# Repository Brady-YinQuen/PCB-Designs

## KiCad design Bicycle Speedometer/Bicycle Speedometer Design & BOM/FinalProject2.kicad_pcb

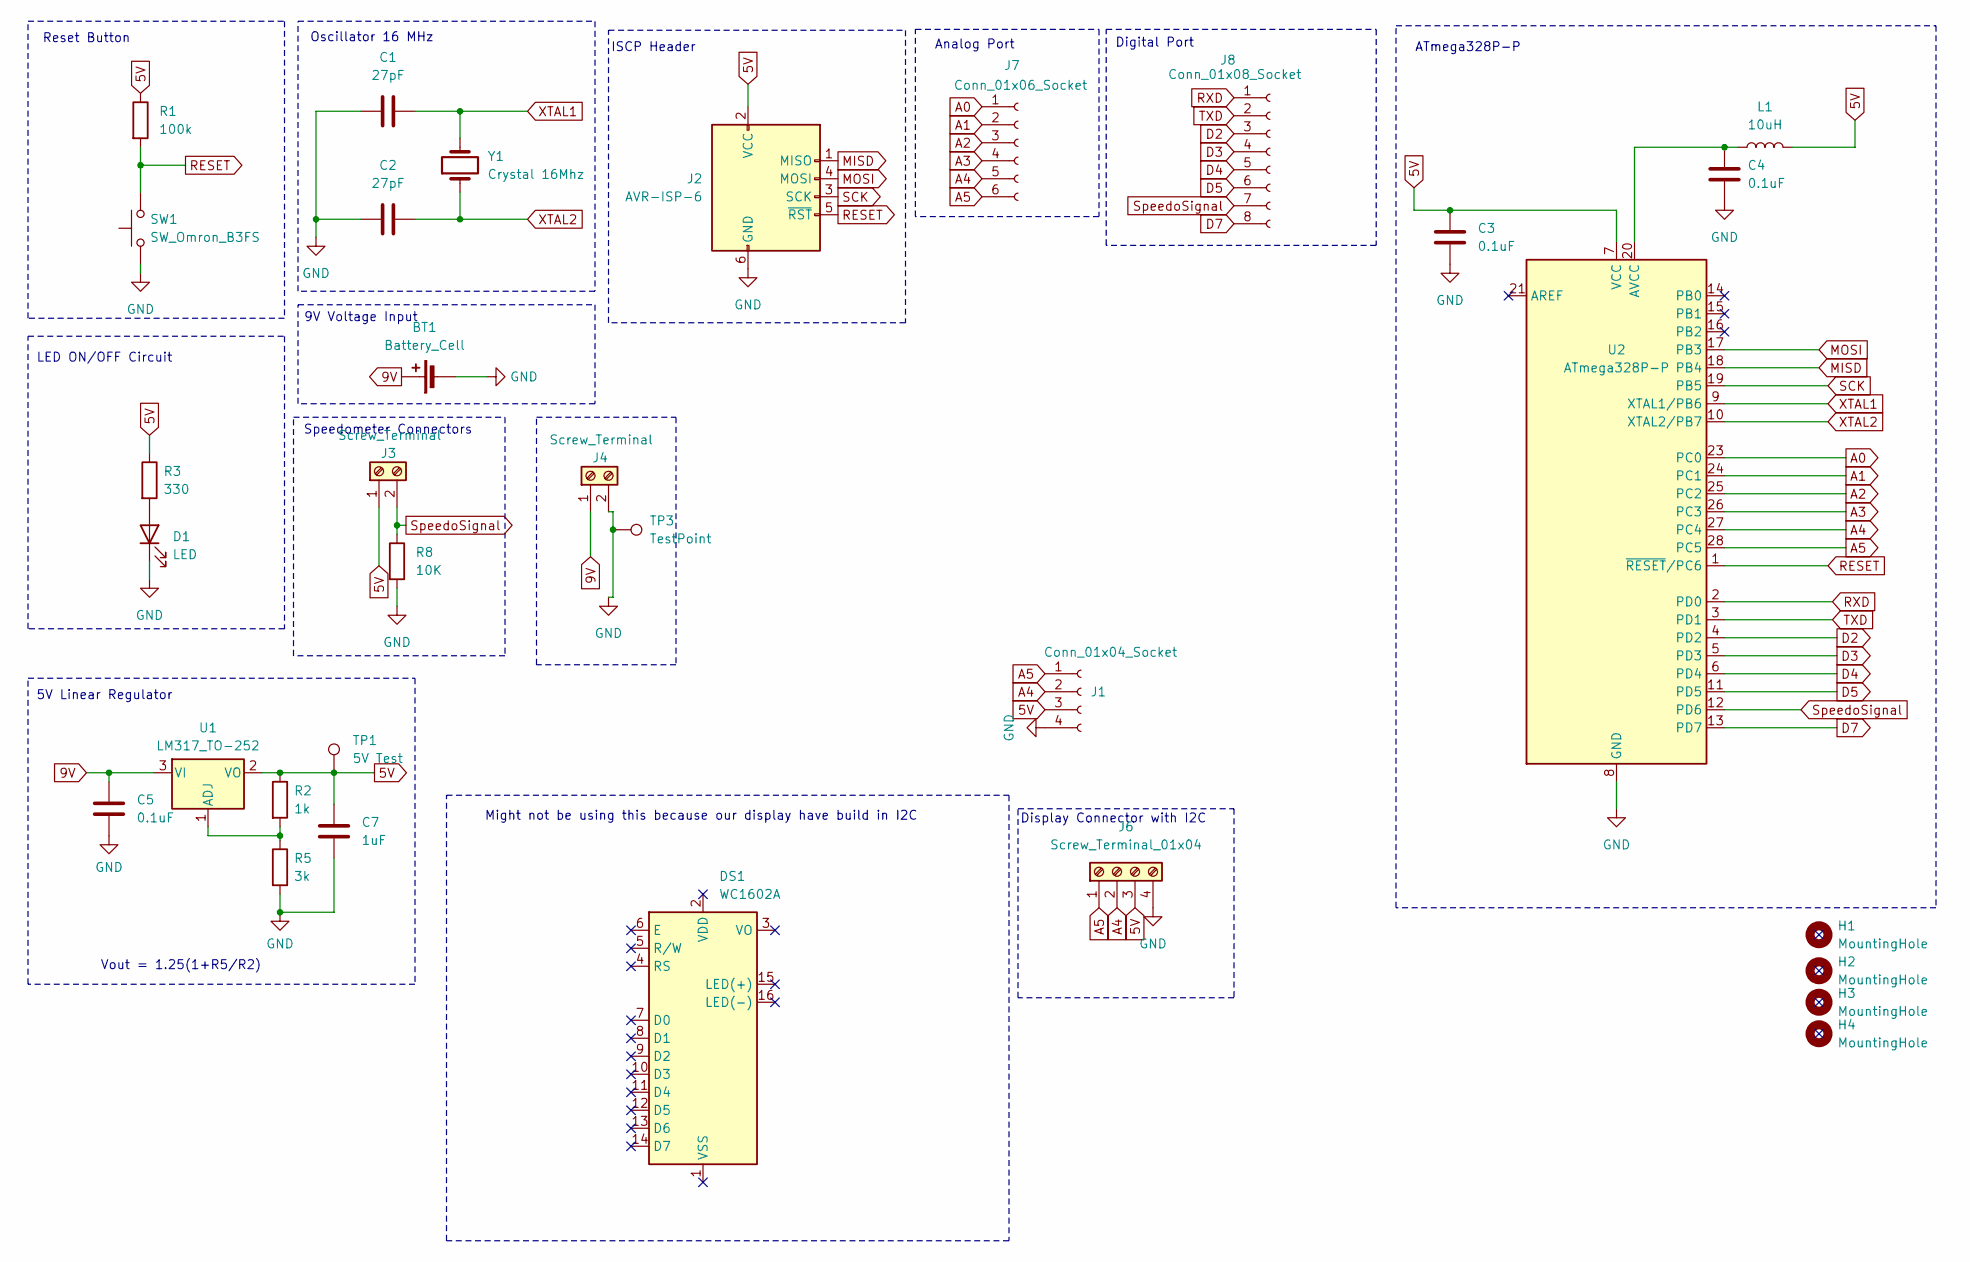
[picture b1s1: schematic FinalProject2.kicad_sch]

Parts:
BT1: Battery_Cell; BatteryHolder_MPD_BA9VPC_1xPP3
C1, C2: 27pF; C_0805_2012Metric_Pad1.18x1.45mm_HandSolder
C3, C4, C5: 0.1uF; C_0805_2012Metric_Pad1.18x1.45mm_HandSolder
C7: 1uF; C_0805_2012Metric_Pad1.18x1.45mm_HandSolder
D1: LED; LED_0805_2012Metric_Pad1.15x1.40mm_HandSolder
DS1: WC1602A
H1, H2, H3, H4: MountingHole; MountingHole_2.2mm_M2_DIN965_Pad
J1: Conn_01x04_Socket; PinSocket_1x04_P2.54mm_Horizontal
J2: AVR-ISP-6; IDC-Header_2x03_P2.54mm_Vertical
J3, J4: Screw_Terminal; TerminalBlock_TE_282834-2_1x02_P2.54mm_Horizontal
J6: Screw_Terminal_01x04; TerminalBlock_Xinya_XY308-2.54-4P_1x04_P2.54mm_Horizontal
J7: Conn_01x06_Socket; PinSocket_1x06_P2.54mm_Vertical
J8: Conn_01x08_Socket; PinSocket_1x08_P2.54mm_Vertical
L1: 10uH; L_0805_2012Metric_Pad1.15x1.40mm_HandSolder
R1: 100k; R_0805_2012Metric_Pad1.20x1.40mm_HandSolder
R2: 1k; R_0805_2012Metric_Pad1.20x1.40mm_HandSolder
R3: 330; R_0805_2012Metric_Pad1.20x1.40mm_HandSolder
R5: 3k; R_0805_2012Metric_Pad1.20x1.40mm_HandSolder
R8: 10K; R_0805_2012Metric_Pad1.20x1.40mm_HandSolder
SW1: SW_Omron_B3FS; SW_SPST_Omron_B3FS-101xP
TP1: 5V Test; Pin_D1.0mm_L10.0mm
TP3: TestPoint; Pin_D1.0mm_L10.0mm
U1: LM317_TO-252; SOT-223-3_TabPin2
U2: ATmega328P-P; DIP-28_W7.62mm
Y1: Crystal 16Mhz; Crystal_SMD_HC49-SD

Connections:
5V: C3.1, C7.1, J1.3, J2.2 (VCC), J3.1, J6.3, L1.2, R1.1, R2.1, R3.1, TP1.1, U1.2 (VO), U2.7 (VCC)
9V: BT1.1 (+), C5.1, J4.1, U1.3 (VI)
A0: J7.1, U2.23 (PC0)
A1: J7.2, U2.24 (PC1)
A2: J7.3, U2.25 (PC2)
A3: J7.4, U2.26 (PC3)
A4: J1.2, J6.2, J7.5, U2.27 (PC4)
A5: J1.1, J6.1, J7.6, U2.28 (PC5)
D2: J8.3, U2.4 (PD2)
D3: J8.4, U2.5 (PD3)
D4: J8.5, U2.6 (PD4)
D5: J8.6, U2.11 (PD5)
D7: J8.8, U2.13 (PD7)
GND: BT1.2 (-), C1.1, C2.1, C3.2, C4.2, C5.2, C7.2, D1.1 (K), J1.4, J2.6 (GND), J4.2, J6.4, R5.2, R8.2, SW1.1, TP3.1, U2.8 (GND), U2.22 (GND)
MISD: J2.1 (MISO), U2.18 (PB4)
MOSI: J2.4 (MOSI), U2.17 (PB3)
unnamed: D1.2 (A), R3.2
unnamed: R2.2, R5.1, U1.1 (ADJ)
unnamed: C4.1, L1.1, U2.20 (AVCC)
RESET: J2.5 (~RST), R1.2, SW1.2, U2.1 (~RESET/PC6)
RXD: J8.1, U2.2 (PD0)
SCK: J2.3 (SCK), U2.19 (PB5)
SpeedoSignal: J3.2, J8.7, R8.1, U2.12 (PD6)
TXD: J8.2, U2.3 (PD1)
XTAL1: C1.2, U2.9 (XTAL1/PB6), Y1.2
XTAL2: C2.2, U2.10 (XTAL2/PB7), Y1.1

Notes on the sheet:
Might not be using this because our display have build in I2C
Vout = 1.25(1+R5/R2)
Oscillator 16 MHz
Digital Port
Reset Button
ATmega328P-P
5V Linear Regulator
Analog Port
ISCP Header
Speedometer Connectors
9V Voltage Input
Display Connector with I2C
LED ON/OFF Circuit

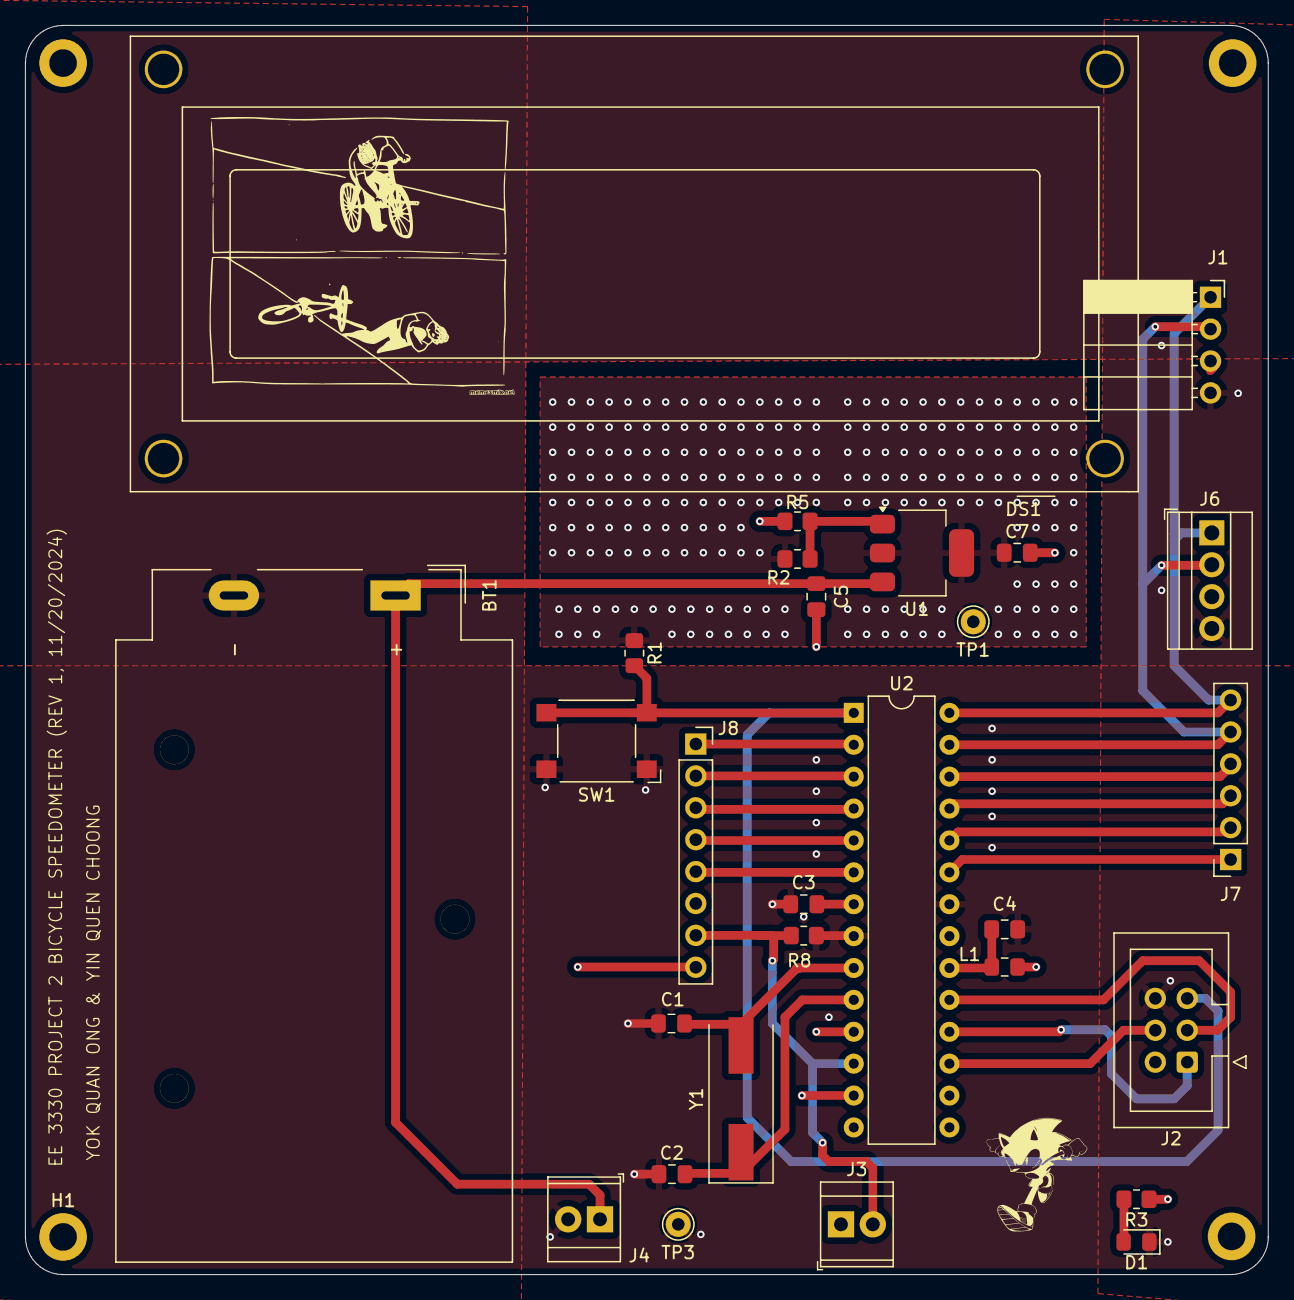
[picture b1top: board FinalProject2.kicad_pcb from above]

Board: 4 copper layers, 99.0 x 99.5 mm, 32 parts (0 on the bottom side), 26 nets.

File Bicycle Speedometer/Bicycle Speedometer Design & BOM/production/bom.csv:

Designator,Footprint,Quantity,Value,LCSC Part #
BT1,BatteryHolder_MPD_BA9VPC_1xPP3,1,Battery_Cell,
"C1, C2",0805,2,27pF,
"C3, C4, C5",0805,3,0.1uF,
C7,0805,1,1uF,
D1,0805,1,LED,
DS1,WC1602A,1,WC1602A,
J1,PinSocket_1x04_P2.54mm_Horizontal,1,Conn_01x04_Socket,
J2,IDC-Header_2x03_P2.54mm_Vertical,1,AVR-ISP-6,
"J3, J4",TerminalBlock_TE_282834-2_1x02_P2.54mm_Horizontal,2,Screw_Terminal,
J6,TerminalBlock_Xinya_XY308-2.54-4P_1x04_P2.54mm_Horizontal,1,Screw_Terminal_01x04,
J7,PinSocket_1x06_P2.54mm_Vertical,1,Conn_01x06_Socket,
J8,PinSocket_1x08_P2.54mm_Vertical,1,Conn_01x08_Socket,
L1,0805,1,10uH,
R1,0805,1,100k,
R2,0805,1,1k,
R3,0805,1,330,
R5,0805,1,3k,
R8,0805,1,10K,
SW1,SW_SPST_Omron_B3FS-101xP,1,SW_Omron_B3FS,
TP1,Pin_D1.0mm_L10.0mm,1,5V Test,
TP3,Pin_D1.0mm_L10.0mm,1,TestPoint,
U1,SOT-223-3_TabPin2,1,LM317_TO-252,
U2,DIP-28_W7.62mm,1,ATmega328P-P,
Y1,Crystal_SMD_HC49-SD,1,Crystal 16Mhz,
